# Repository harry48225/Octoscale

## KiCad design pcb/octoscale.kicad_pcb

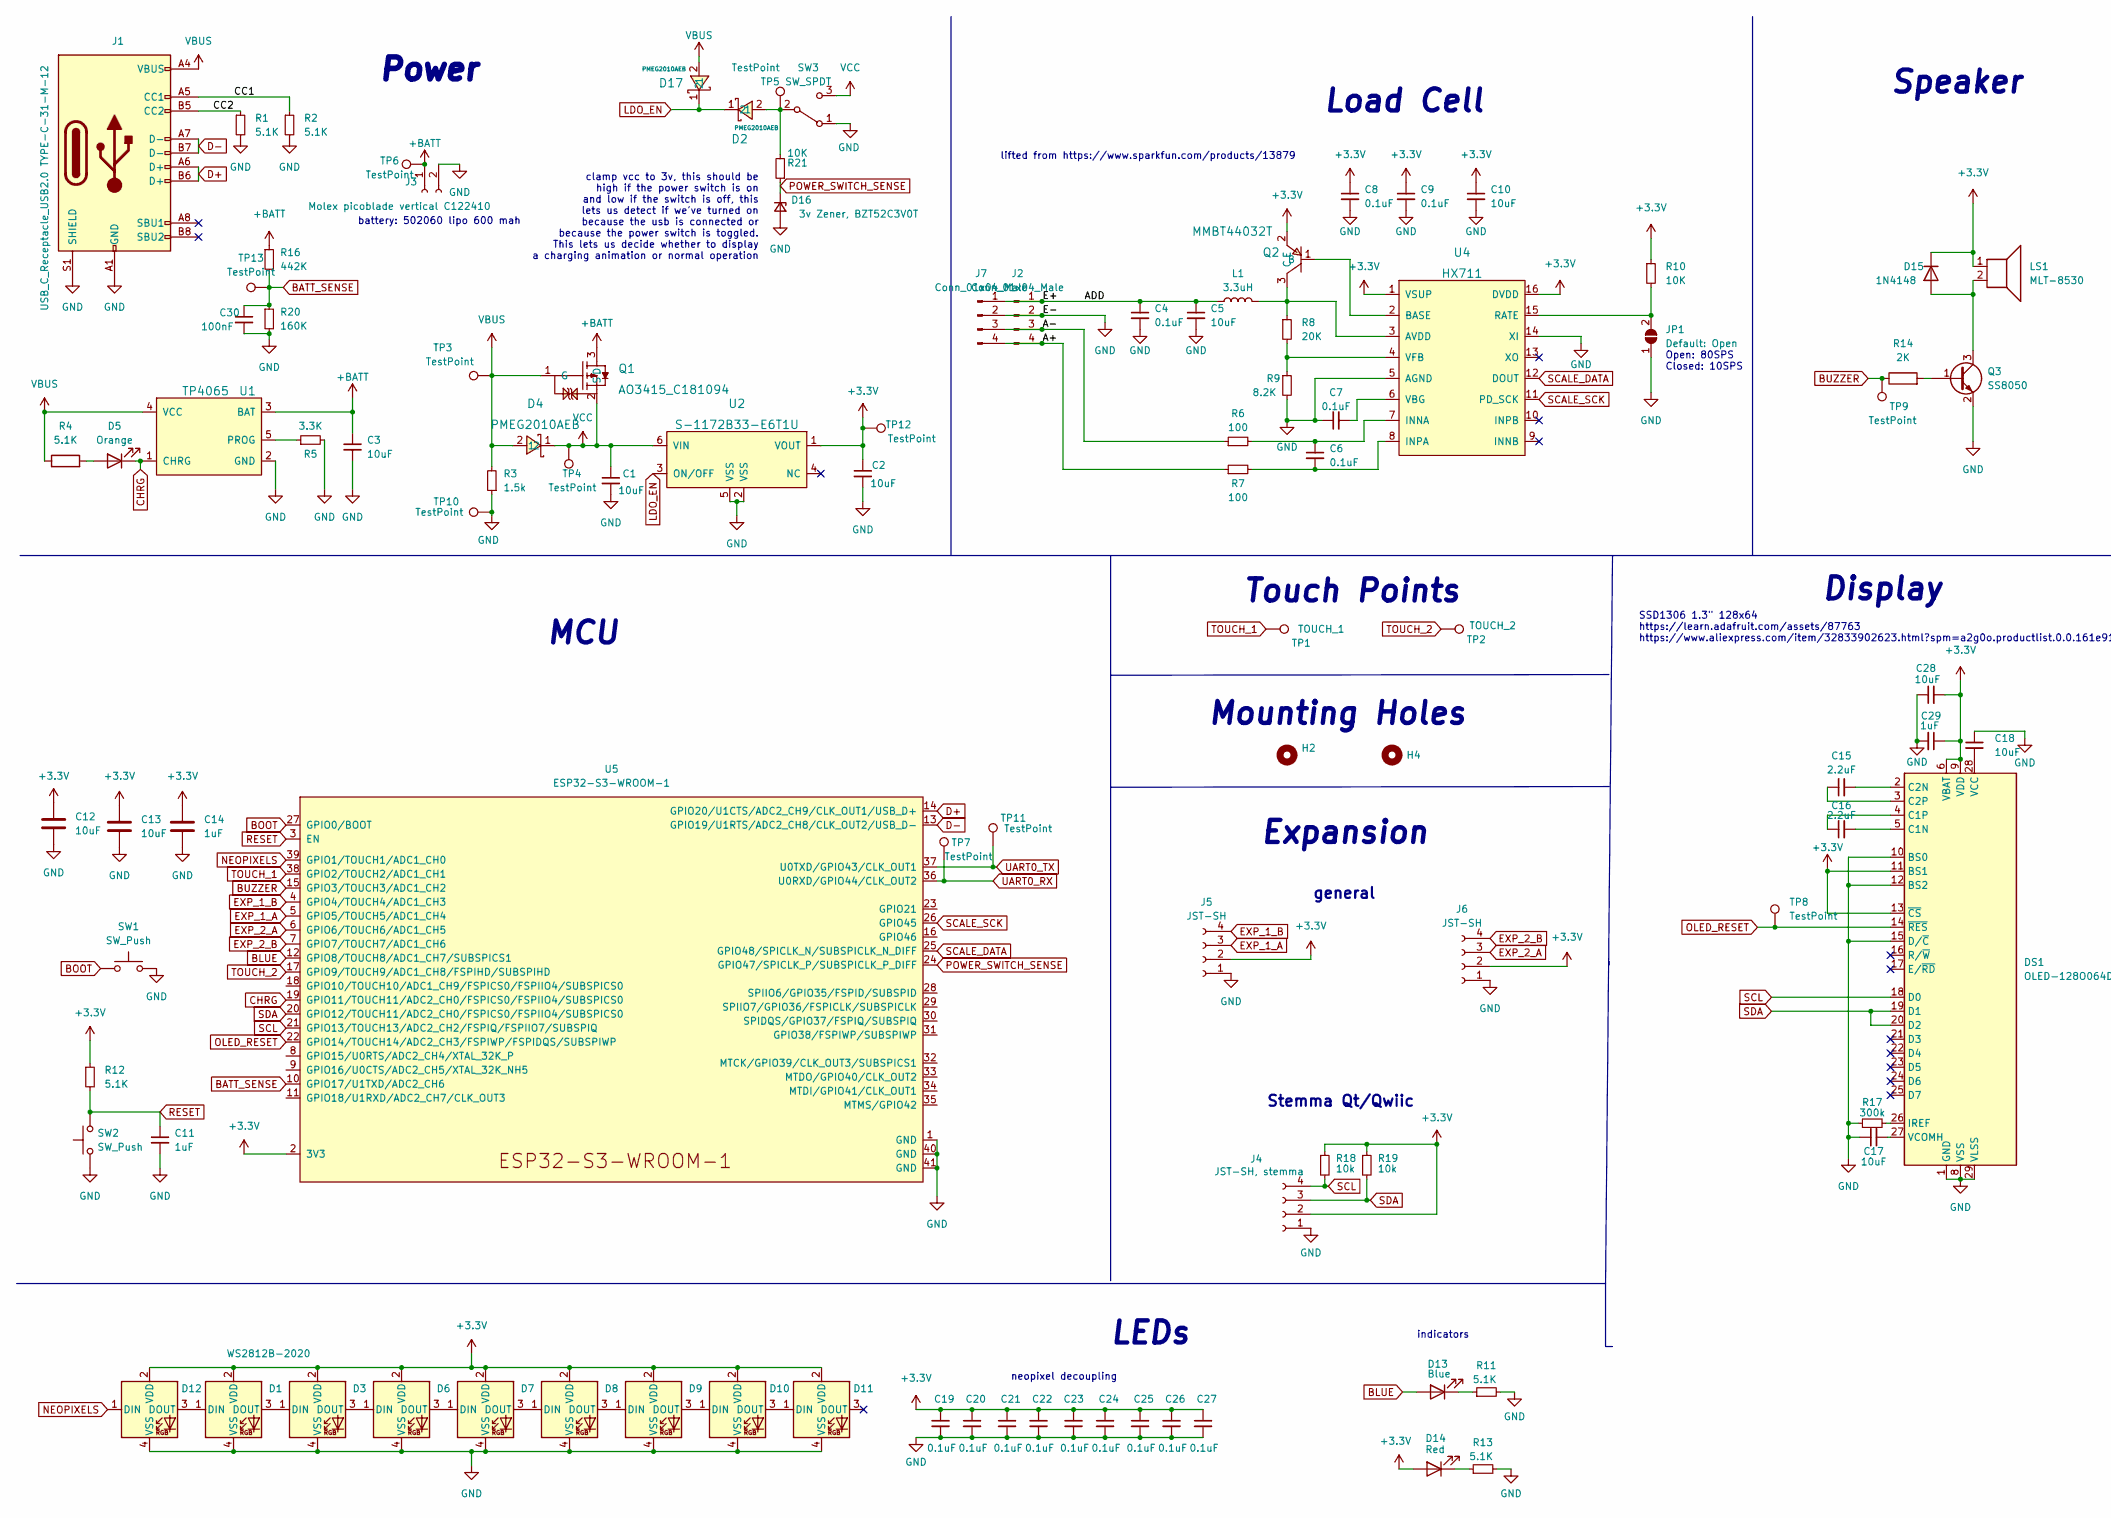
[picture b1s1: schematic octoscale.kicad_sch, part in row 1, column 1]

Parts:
C1, C2, C3, C5, C10, C12, C13, C17, C18, C28: 10uF; C_0805_2012Metric_Pad1.18x1.45mm_HandSolder
C4, C6, C7, C8, C9, C19, C20, C21, C22, C23, C24, C25, C26, C27: 0.1uF; C_0805_2012Metric_Pad1.18x1.45mm_HandSolder
C11, C14, C29: 1uF; C_0805_2012Metric_Pad1.18x1.45mm_HandSolder
C15, C16: 2.2uF; C_0805_2012Metric_Pad1.18x1.45mm_HandSolder
C30: 100nF; C_0805_2012Metric_Pad1.18x1.45mm_HandSolder
D1, D3, D6, D7, D8, D9, D10, D11, D12: WS2812B-2020; LED-SMD_4P-L2.0-W2.0-TL_WS2812B-2020
D2, D4, D17: PMEG2010AEB; D_SOD-523; LCSC Part C282563
D5: Orange; LED_0805_2012Metric_Pad1.15x1.40mm_HandSolder
D13: Blue; LED_0805_2012Metric_Pad1.15x1.40mm_HandSolder
D14: Red; LED_0805_2012Metric_Pad1.15x1.40mm_HandSolder
D15: 1N4148; D_SOD-323_HandSoldering
D16: 3v Zener, BZT52C3V0T; D_SOD-323
DS1: OLED-128O064D
H2, H4: MountingHole; MountingHole_2.7mm_M2.5
J1: USB_C_Receptacle_USB2.0 TYPE-C-31-M-12; USB-C_SMD-TYPE-C-31-M-12
J2, J7: Conn_01x04_Male; JST_SH_BM04B-SRSS-TB_1x04-1MP_P1.00mm_Vertical
J3: Molex picoblade vertical C122410; Molex_PicoBlade_53398-0271_1x02-1MP_P1.25mm_Vertical
J4: JST-SH, stemma; JST_SH_BM04B-SRSS-TB_1x04-1MP_P1.00mm_Vertical
J5, J6: JST-SH; JST_SH_BM04B-SRSS-TB_1x04-1MP_P1.00mm_Vertical
JP1: Default: Open; SolderJumper-2_P1.3mm_Open_TrianglePad1.0x1.5mm
L1: 3.3uH; L_0805_2012Metric_Pad1.05x1.20mm_HandSolder
LS1: MLT-8530; MagneticBuzzer_Kobitone_254-EMB84Q-RO
Q1: AO3415_C181094; SOT-23-3_L2.9-W1.3-P1.90-LS2.4-BR; LCSC Part C181094
Q2: MMBT44032T; SOT-23-3_L2.9-W1.3-P1.90-LS2.4-BR; LCSC Part C8513
Q3: SS8050; SOT-23
R1, R2, R4, R11, R12, R13: 5.1K; R_0805_2012Metric_Pad1.20x1.40mm_HandSolder
R3: 1.5k; R_0805_2012Metric_Pad1.20x1.40mm_HandSolder
R5: 3.3K; R_0805_2012Metric_Pad1.20x1.40mm_HandSolder
R6, R7: 100; R_0805_2012Metric_Pad1.20x1.40mm_HandSolder
R8: 20K; R_0805_2012Metric_Pad1.20x1.40mm_HandSolder
R9: 8.2K; R_0805_2012Metric_Pad1.20x1.40mm_HandSolder
R10, R21: 10K; R_0805_2012Metric_Pad1.20x1.40mm_HandSolder
R14: 2K; R_0805_2012Metric_Pad1.20x1.40mm_HandSolder
R16: 442K; R_0805_2012Metric_Pad1.20x1.40mm_HandSolder
R17: 300k; R_0805_2012Metric_Pad1.20x1.40mm_HandSolder
R18, R19: 10k; R_0805_2012Metric_Pad1.20x1.40mm_HandSolder
R20: 160K; R_0805_2012Metric_Pad1.20x1.40mm_HandSolder
SW1, SW2: SW_Push; SW_Push_1P1T_NO_CK_KMR2
SW3: SW_SPDT; SW_SPDT_PCM12
TP1: TOUCH_1; TouchPad
TP2: TOUCH_2; TouchPad
TP3, TP4, TP5, TP6, TP7, TP8, TP9, TP10, TP11, TP12, TP13: TestPoint; TestPoint_Pad_D1.5mm
U1: TP4065; SOT-23-5_L3.0-W1.7-P0.95-LS2.8-BR; LCSC Part C113540
U2: S-1172B33-E6T1U; HSOP-6_L5.0-W3.9-P1.91-LS6.0-BL; LCSC Part C140913
U4: HX711; SOP-16_L10.0-W3.9-P1.27-LS6.0-BL; LCSC Part C43656
U5: ESP32-S3-WROOM-1

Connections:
+3.3V: C2.1, C8.1, C9.1, C10.1, C12.1, C13.1, C14.1, C19.1, C20.1, C21.1, C22.1, C23.1, C24.1, C25.1, C26.1, C27.1, C28.2, C29.1, D1.2 (VDD), D3.2 (VDD), D6.2 (VDD), D7.2 (VDD), D8.2 (VDD), D9.2 (VDD), D10.2 (VDD), D11.2 (VDD), D12.2 (VDD), D14.2 (A), D15.1 (K), DS1.6 (VBAT), DS1.9 (VDD), DS1.11 (BS1), DS1.13 (~CS), J4.2, J5.2, J6.2, LS1.1, Q2.2 (E), R10.1, R12.1, R18.1, R19.1, TP12.1, U2.1 (VOUT), U4.1 (VSUP), U4.16 (DVDD), U5.2 (3V3)
+BATT: C3.1, J3.1, Q1.3 (D), R16.1, TP6.1, U1.3 (BAT)
/A+: J2.4, J7.4, R7.1
/A-: J2.3, J7.3, R6.1
/ADD: C4.1, C5.1, J2.1, J7.1, L1.1
/CC1: J1.A5 (CC1), R2.1
/CC2: J1.B5 (CC2), R1.1
BATT_SENSE: C30.1, R16.2, R20.1, TP13.1, U5.10 (GPIO17/U1TXD/ADC2_CH6)
BLUE: D13.2 (A), U5.12 (GPIO8/TOUCH8/ADC1_CH7/SUBSPICS1)
BOOT: SW1.1, U5.27 (GPIO0/BOOT)
BUZZER: R14.1, TP9.1, U5.15 (GPIO3/TOUCH3/ADC1_CH2)
CHRG: D5.1 (K), U1.1 (CHRG), U5.19 (GPIO11/TOUCH11/ADC2_CH0/FSPICS0/FSPIIO4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)
D+: J1.A6 (D+), J1.B6 (D+), U5.14 (GPIO20/U1CTS/ADC2_CH9/CLK_OUT1/USB_D+)
D-: J1.A7 (D-), J1.B7 (D-), U5.13 (GPIO19/U1RTS/ADC2_CH8/CLK_OUT2/USB_D-)
EXP_1_A: J5.3, U5.5 (GPIO5/TOUCH5/ADC1_CH4)
EXP_1_B: J5.4, U5.4 (GPIO4/TOUCH4/ADC1_CH3)
EXP_2_A: J6.3, U5.6 (GPIO6/TOUCH6/ADC1_CH5)
EXP_2_B: J6.4, U5.7 (GPIO7/TOUCH7/ADC1_CH6)
GND: C1.2, C2.2, C3.2, C4.2, C5.2, C7.1, C8.2, C9.2, C10.2, C11.2, C12.2, C13.2, C14.2, C17.1, C18.1, C19.2, C20.2, C21.2, C22.2, C23.2, C24.2, C25.2, C26.2, C27.2, C28.1, C29.2, C30.2, D1.4 (VSS), D3.4 (VSS), D6.4 (VSS), D7.4 (VSS), D8.4 (VSS), D9.4 (VSS), D10.4 (VSS), D11.4 (VSS), D12.4 (VSS), D16.2 (A), DS1.1 (GND), DS1.8 (VSS), DS1.10 (BS0), DS1.12 (BS2), DS1.15 (D/~C), DS1.29 (VLSS), DS1.30 (GND), J1.A1 (GND), J1.A12 (GND), J1.B1 (GND), J1.B12 (GND), J1.S1 (SHIELD), J2.2, J3.2, J4.1, J5.1, J6.1, J7.2, JP1.1 (A), Q3.2 (E), R1.2, R2.2, R3.1, R5.2, R9.2, R11.2, R13.2, R17.1, R20.2, SW1.2, SW2.1, SW3.1 (A), TP10.1, U1.2 (GND), U2.2 (VSS), U2.5 (VSS), U4.5 (AGND), U4.14 (XI), U5.1 (GND), U5.40 (GND), U5.41 (GND)
LDO_EN: D2.1, D17.1, U2.3 (ON/OFF)
NEOPIXELS: D12.1 (DIN), U5.39 (GPIO1/TOUCH1/ADC1_CH0)
unnamed: C6.1, R6.2, U4.7 (INNA)
unnamed: C6.2, R7.2, U4.8 (INPA)
unnamed: C7.2, U4.6 (VBG)
unnamed: C15.1, DS1.3 (C2P)
unnamed: C15.2, DS1.2 (C2N)
unnamed: C16.1, DS1.4 (C1P)
unnamed: C16.2, DS1.5 (C1N)
unnamed: C17.2, DS1.27 (VCOMH)
unnamed: C18.2, DS1.28 (VCC)
unnamed: D1.1 (DIN), D12.3 (DOUT)
unnamed: D1.3 (DOUT), D3.1 (DIN)
unnamed: D2.2, R21.2, SW3.2 (B), TP5.1
unnamed: D3.3 (DOUT), D6.1 (DIN)
unnamed: D5.2 (A), R4.2
unnamed: D6.3 (DOUT), D7.1 (DIN)
unnamed: D7.3 (DOUT), D8.1 (DIN)
unnamed: D8.3 (DOUT), D9.1 (DIN)
unnamed: D9.3 (DOUT), D10.1 (DIN)
unnamed: D10.3 (DOUT), D11.1 (DIN)
unnamed: D13.1 (K), R11.1
unnamed: D14.1 (K), R13.1
unnamed: D15.2 (A), LS1.2, Q3.3 (C)
unnamed: DS1.26 (IREF), R17.2
unnamed: JP1.2 (B), R10.2, U4.15 (RATE)
unnamed: L1.2, Q2.3 (C), R8.1, U4.3 (AVDD)
unnamed: Q2.1 (B), U4.2 (BASE)
unnamed: Q3.1 (B), R14.2
unnamed: R5.1, U1.5 (PROG)
unnamed: R8.2, R9.1, U4.4 (VFB)
OLED_RESET: DS1.14 (~RES), TP8.1, U5.22 (GPIO14/TOUCH14/ADC2_CH3/FSPIWP/FSPIDQS/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)
POWER_SWITCH_SENSE: D16.1 (K), R21.1, U5.24 (GPIO47/SPICLK_P/SUBSPICLK_P_DIFF)
RESET: C11.1, R12.2, SW2.2, U5.3 (EN)
SCALE_DATA: U4.12 (DOUT), U5.25 (GPIO48/SPICLK_N/SUBSPICLK_N_DIFF)
SCALE_SCK: U4.11 (PD_SCK), U5.26 (GPIO45)
SCL: DS1.18 (D0), J4.4, R18.2, U5.21 (GPIO13/TOUCH13/ADC2_CH2/FSPIQ/FSPIIO7/S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)
SDA: DS1.19 (D1), DS1.20 (D2), J4.3, R19.2, U5.20 (GPIO12/TOUCH11/ADC2_CH0/FSPICS0/FSPIIO4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)
TOUCH_1: TP1.1, U5.38 (GPIO2/TOUCH2/ADC1_CH1)
TOUCH_2: TP2.1, U5.17 (GPIO9/TOUCH9/ADC1_CH8/FSPIHD/SUBSPIHD)
UART0_RX: TP7.1, U5.36 (U0RXD/GPIO44/CLK_OUT2)
UART0_TX: TP11.1, U5.37 (U0TXD/GPIO43/CLK_OUT1)
VBUS: D4.2, D17.2, J1.A4 (VBUS), J1.A9 (VBUS), J1.B4 (VBUS), J1.B9 (VBUS), Q1.1 (G), R3.2, R4.1, TP3.1, U1.4 (VCC)
VCC: C1.1, D4.1, Q1.2 (S), SW3.3 (C), TP4.1, U2.6 (VIN)

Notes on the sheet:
lifted from https://www.sparkfun.com/products/13879
Open: 80SPS Closed: 10SPS
Touch Points
MCU
Power
battery: 502060 lipo 600 mah
Display
Expansion
Mounting Holes
SSD1306 1.3" 128x64 https://learn.adafruit.com/assets/87763 https://www.aliexpress.com/item/32833902623.html?spm=a2g0o.productlist.0.0.161e9124agGbN2&algo_pvid=128955a3-e0d0-4f90-829f-11a06950333c&algo_exp_id=128955a3-e0d0-4f90-829f-11a06950333c-10&pdp_ext_f=%7B%22sku_id%22%3A%2265420055737%22%7D&p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
clamp vcc to 3v, this should be high if the power switch is on and low if the switch is off, this lets us detect if we've turned on because the usb is connected or because the power switch is toggled. This lets us decide whether to display a charging animation or normal operation
Stemma Qt/Qwiic
LEDs
Speaker
Load Cell
neopixel decoupling
general
indicators

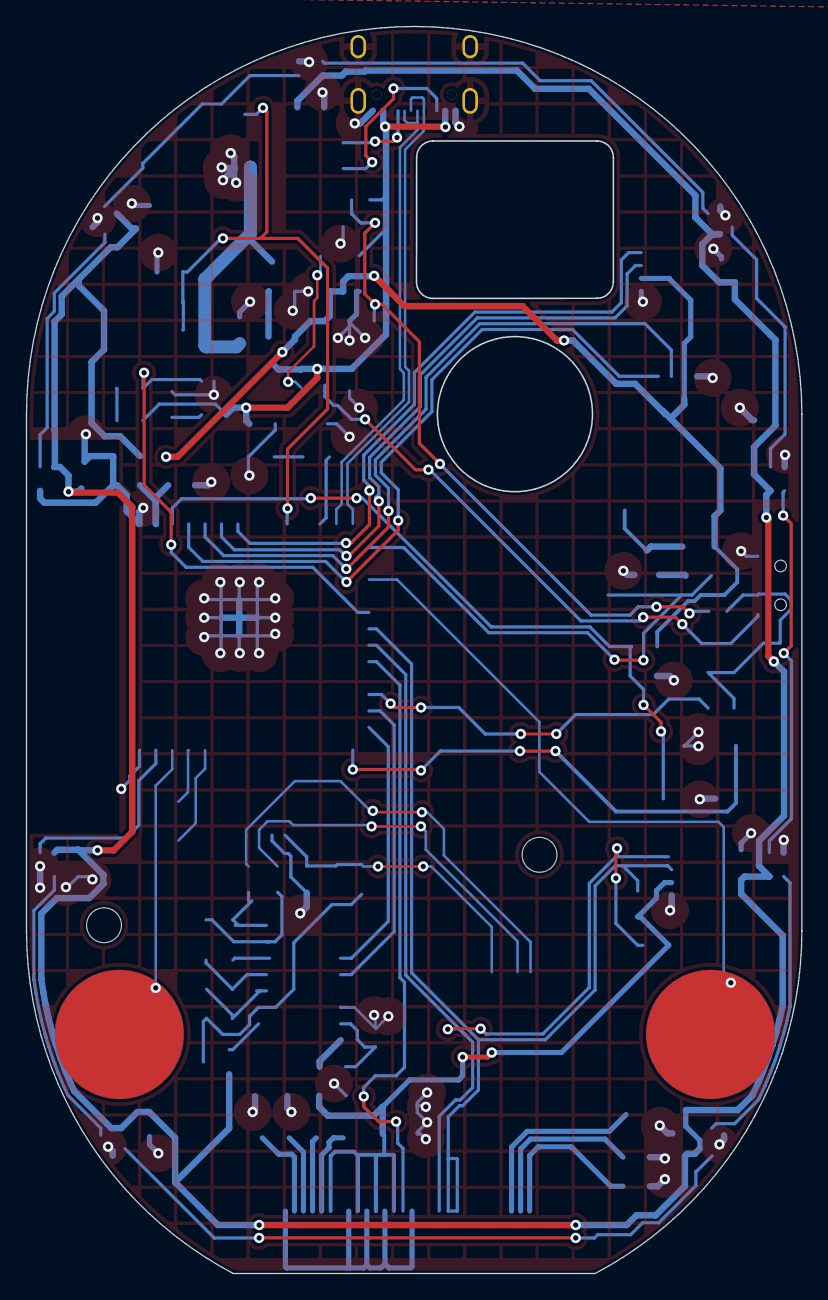
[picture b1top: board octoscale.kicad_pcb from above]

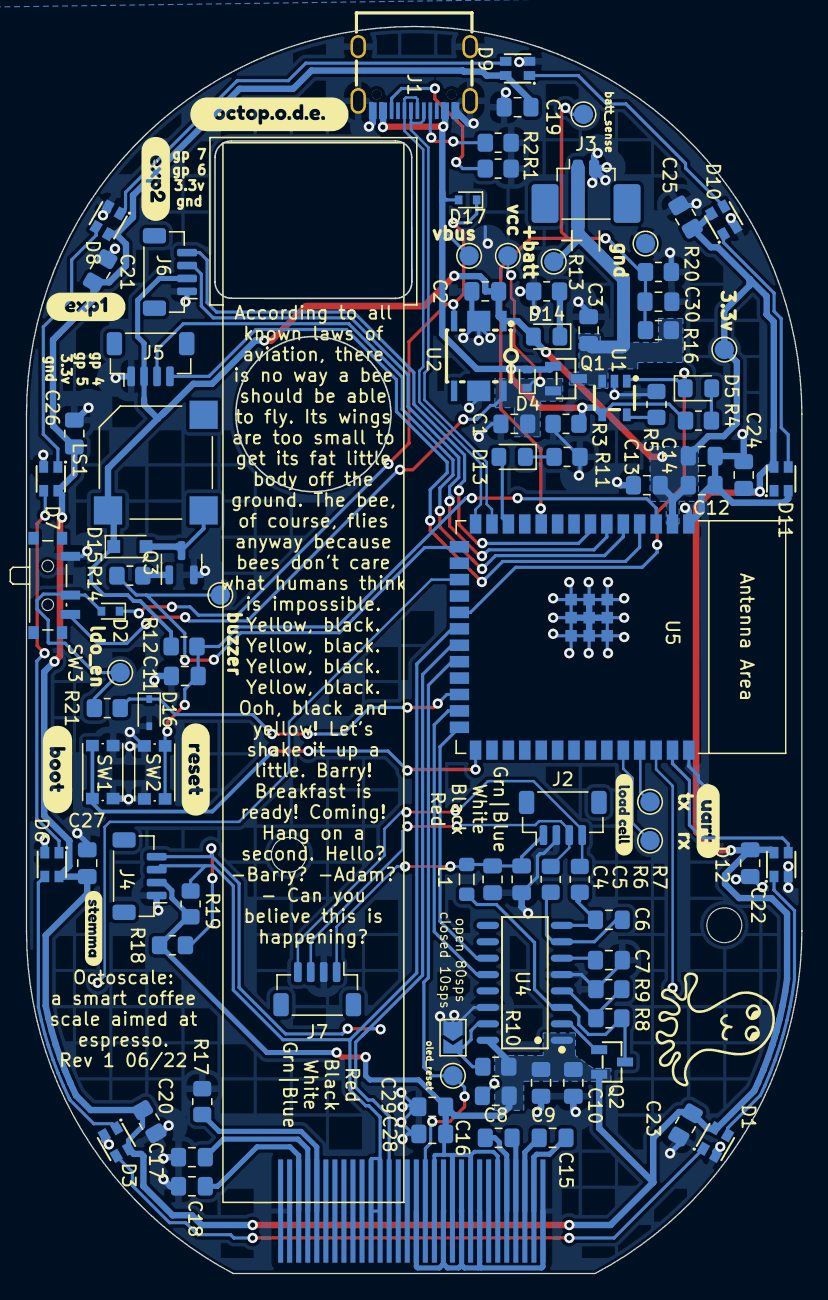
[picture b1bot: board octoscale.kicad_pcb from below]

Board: 2 copper layers, 60.0 x 96.5 mm, 111 parts (107 on the bottom side), 63 nets.

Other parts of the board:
kibuzzard-62A1FF38: G***; kibuzzard-62A1FF38
kibuzzard-629CD677: G***; kibuzzard-629CD677
kibuzzard-629CD693: G***; kibuzzard-629CD693
kibuzzard-629CDB8B: G***; kibuzzard-629CDB8B
kibuzzard-629CE03A: G***; kibuzzard-629CE03A
kibuzzard-629E3B4E: G***; kibuzzard-629E3B4E
kibuzzard-629E3B7C: G***; kibuzzard-629E3B7C
kibuzzard-629E3091: G***; kibuzzard-629E3091

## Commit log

2022-05-08 Basic scale example
2022-05-08 Improve calibration routine
2022-05-08 Add faster scale reading
2022-05-08 Add 1 euro filter
2022-05-15 Refavtor scale into class
2022-05-15 Tweak tuning
2022-05-15 Add settled detection
2022-05-15 Add autotimer
2022-05-15 Convert timer to mins and seconds
2022-05-15 Add autostop
2022-05-15 Add auto tare
2022-05-15 move tare from hx711 to scale class
2022-05-15 Improve autotare
2022-05-15 Tune settling detecting
2022-05-16 Add asymmetrical unsettling
2022-05-17 Add graph drawing routine
2022-05-17 Make graph track brew weight
2022-05-25 Add thinning to reduce number of data points
2022-05-29 Improve settling detection
2022-05-29 improve auto tare
2022-05-29 Improve display
2022-05-29 Refactor graph
2022-05-29 Refactor timer
2022-05-29 refactor autotare
2022-05-29 Add brew statistics
2022-05-29 Improve brew stats screen
2022-05-29 stop graph when timer primed
2022-05-31 add ble mass broadcasting
2022-05-31 Add blank svelte app
2022-05-31 basic scale connection
2022-05-31 Decode characteristic
2022-05-31 Interpolate mass values
2022-06-01 Increase precision of bluetooth transmission
2022-06-01 Refactor bluetooth
2022-06-01 style mass display
2022-06-01 Add tare characteristic
2022-06-01 add is timing characteristic
2022-06-01 Add timer duration characteristic
2022-06-01 Add tare to app
2022-06-01 Use the constants in bleManager
2022-06-01 Added timing notifcation
2022-06-02 Change mass to notify
2022-06-02 Add timer duration to app
2022-06-02 Improve timer styling
2022-06-02 Basic restyle
2022-06-02 Show timer only when timing
2022-06-09 consolidate files
2022-06-09 Model load cell
2022-06-09 Add battery
2022-06-09 Try different battery sizes
2022-06-09 Move load cell
2022-06-09 Move battery connector
2022-06-09 first draft of case
2022-06-09 add lipo cavity
2022-06-10 Swap load cell
2022-06-12 Decrease ble power usage by ~33%
2022-06-12 Fix calibration routine
2022-06-12 Change battery connector and load cell
2022-06-12 Bottom of case
2022-06-12 Add load cell mounting to top
2022-06-12 Add usb c port
2022-06-12 Tweak height clearance
2022-06-22 Change oled to ssd1306 and fix hx711 agnd
2022-06-22 Minor tweaks
2022-06-22 Move touch 2 pins
2022-06-22 Add charge detection
2022-06-22 Remove ground fill from under esp32
2022-06-22 Add batt_sense test point
2022-06-22 tweak batt sense silk
2022-06-26 Tweak to layout and power ldo en
2022-06-26 Tweak charging speed
2022-06-26 Move Batt sense to adc capable pin
2022-06-27 Change zener footprint
2022-06-28 Fix neopixel footprint
2022-06-30 Slight tweaks
2022-07-03 Add snail graphic
2022-07-03 Generate gerbers
2022-07-04 pcb tweaks
2022-07-05 Tidy app
2022-07-05 Implement settings page navigation
2022-07-05 Create basic slider component
2022-07-05 Tweak setting sliders
2022-07-05 Add action buttons to settings
2022-07-05 Add connected banner to settings
2022-07-05 Apply global styling
2022-07-10 Basic slider implementation with variable stepSize
2022-08-05 Create number field
2022-08-05 Update slider setting
2022-08-05 Misc pcb changes
2022-08-05 Refactor NumberField
2022-08-05 Add min and max for sliders
2022-08-05 Tweak slider
2022-08-05 Add margin to settings page
2022-08-05 Recolour app
2022-08-06 Change padding
2022-08-06 Add bottom navigation bar to home page
2022-08-06 Add navigation bar to settings page
2022-08-06 Commonise some styles
2022-08-07 Convert home to 2 spcaes
2022-08-07 Refactor setting fields
2022-08-07 Style slider
2022-08-07 Create settings section
2022-08-07 Refactor action buttons
2022-08-07 Create slider setting
2022-08-07 Add more settings
2022-08-07 General styling tweaks
2022-08-07 Add lighting setting
2022-08-07 Change status bar colour
2022-08-07 Add canvas
2022-08-07 Add basic canvas demo
2022-08-07 Add basic graph drawing
2022-08-07 Style graph
2022-08-07 Add more example graph data
2022-08-07 Attempt to change splash screen
2022-08-07 Revert changes
2022-08-08 Add ticks
2022-08-29 Add top mounting holes
2022-08-29 reduce acrylic thickness
2022-08-30 Increase toggle length
2022-08-30 generate bom
2022-08-30 increase slider length
2022-08-30 Fix slider placement
2022-08-30 more slider tweaks
2022-08-30 Small tweaks
2022-08-31 Initial tweaks to get working on pcb
2022-08-31 Tweak config
2022-08-31 Fix config
2022-08-31 Add embedded nuts
2022-09-01 Adjust lcd mounting
2022-09-01 add display cut out
2022-09-01 basic touch buttons
2022-09-02 Improve button handling
2022-09-02 Enlarge oled cut out
2022-09-02 model window
2022-09-02 increase window tolerance
2022-09-02 tweak sensitivity
2022-09-02 garbled display
2022-09-02 fix display
2022-09-02 tweak button sensitivity
2022-09-02 slight refactor
2022-09-02 refactor display
2022-09-02 improve taring
2022-09-02 add led button feedback
2022-09-02 add tare animate
2022-09-02 squashed bug
2022-09-02 fix -0.0 bug
2022-09-02 center mass display
2022-09-03 tune filter
2022-09-04 remove window
2022-09-04 add captive window
2022-09-04 tweak window
2022-09-04 change display cut out
2022-09-04 change fillet
2022-09-04 enlarge holes
2022-09-04 tune parameters
2022-09-04 improve tare routine
2022-09-04 tune button
2022-09-04 add debug serial
2022-09-04 improve timer priming
2022-09-04 add mass to timer screen
2022-09-04 improve timing states
2022-09-04 add ability to cancel timer when primed
2022-09-06 improve button senstivity
2022-09-06 improve timer behaviour
2022-09-06 improve timer
2022-09-06 refactor buttons code
2022-09-06 fix led bug
2022-09-06 adjust slider
2022-09-06 case tweaks
2022-09-07 fix power on bug
2022-09-07 bit banged speaker
2022-09-09 improve speaker
2022-09-09 improve button handlng
2022-09-09 fix touch sensor bug
2022-09-09 add icons for touch target
2022-09-10 remove unessesary duration parameter
2022-09-10 add beep function
2022-09-10 add show countdown
2022-09-10 add startWithCountdown
2022-09-10 improve start timer conditions
2022-09-10 improve timer countdown
2022-09-14 improve bluetooth connection
2022-09-14 add bluetooth buttons
2022-09-14 add bluetooth sprite
2022-09-14 fix not enough handles
2022-09-15 reduce clear amount
2022-09-15 update packages
2022-09-15 tweak buttons
2022-09-15 update buttons
2022-09-15 basic graph updating
2022-09-15 improve graph drawing
2022-09-15 fix some graph jitter
2022-09-15 remove code
2022-09-15 remove more
2022-09-15 fix navigation bug
2022-09-23 update nativescript
2022-09-23 reduce graph update frequency
2022-09-23 increase graph size
2022-09-23 add reset graph
2022-09-23 force graph to start at zero
2022-09-23 fix formatting
2022-09-23 Add timer
2022-09-23 sandwich acrylic more
2022-09-23 add battery sprites
2022-09-23 add battery voltage sensing
2022-09-23 return charge level
2022-09-23 add charging detection
2022-09-24 improve charging dectection
2022-09-24 add power switch sense
2022-09-24 add charging and sleeping state
2022-09-24 add charging animation
2022-09-24 add charging screen
2022-09-24 remove ibom
2022-09-26 add sleep charged state
2022-09-26 refactor main loop
2022-09-26 remove charging screen
2022-09-26 slow down sleep loop
2022-09-26 start migration to canvas-ui
2022-09-26 add new line drawing
2022-09-26 flip axis
2022-09-26 add line cap
2022-09-26 add filled region
2022-09-26 remove old code
2022-09-26 add horizontal ticks
2022-09-26 fix y scale
2022-09-27 add preinfusion
2022-09-27 add carosel library
2022-09-27 style carousel
2022-09-27 add more brew controls
2022-09-27 adjust data scale based on brew design
2022-09-27 add target line
2022-09-27 update graph data only when timing
2022-09-27 send timing stopped ble signal
2022-09-27 dont hide timer
2022-09-27 change to dashed target line
2022-09-27 connection improvements
2022-09-27 fix battery icon bug
2022-09-27 add icon and splash screen
2022-09-27 set app name
2022-09-27 fix name
2022-09-27 polish
2022-09-27 add slight zero offset
2022-09-27 improve displayed mass
2022-09-27 fix sleep bugs
2022-09-28 improve battery monitoring
2022-09-28 remove voltage display
2022-09-29 calibrate
2022-09-30 only show battery warning when power on
2022-10-02 small graph tweaks
2022-11-01 basic schematic and pcb changes
2022-11-03 fix speaker transistor
2022-11-03 Fix buzzer footprint
2022-11-08 Fix drc errors
2022-11-08 Add silk screen
2022-11-08 generate gerbers and update revision number
